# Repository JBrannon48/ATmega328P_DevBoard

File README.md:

# ATmega328P_DevBoard
Created By: Jack Brannon
Made this in a day for Purdue SoCET: Intro I.

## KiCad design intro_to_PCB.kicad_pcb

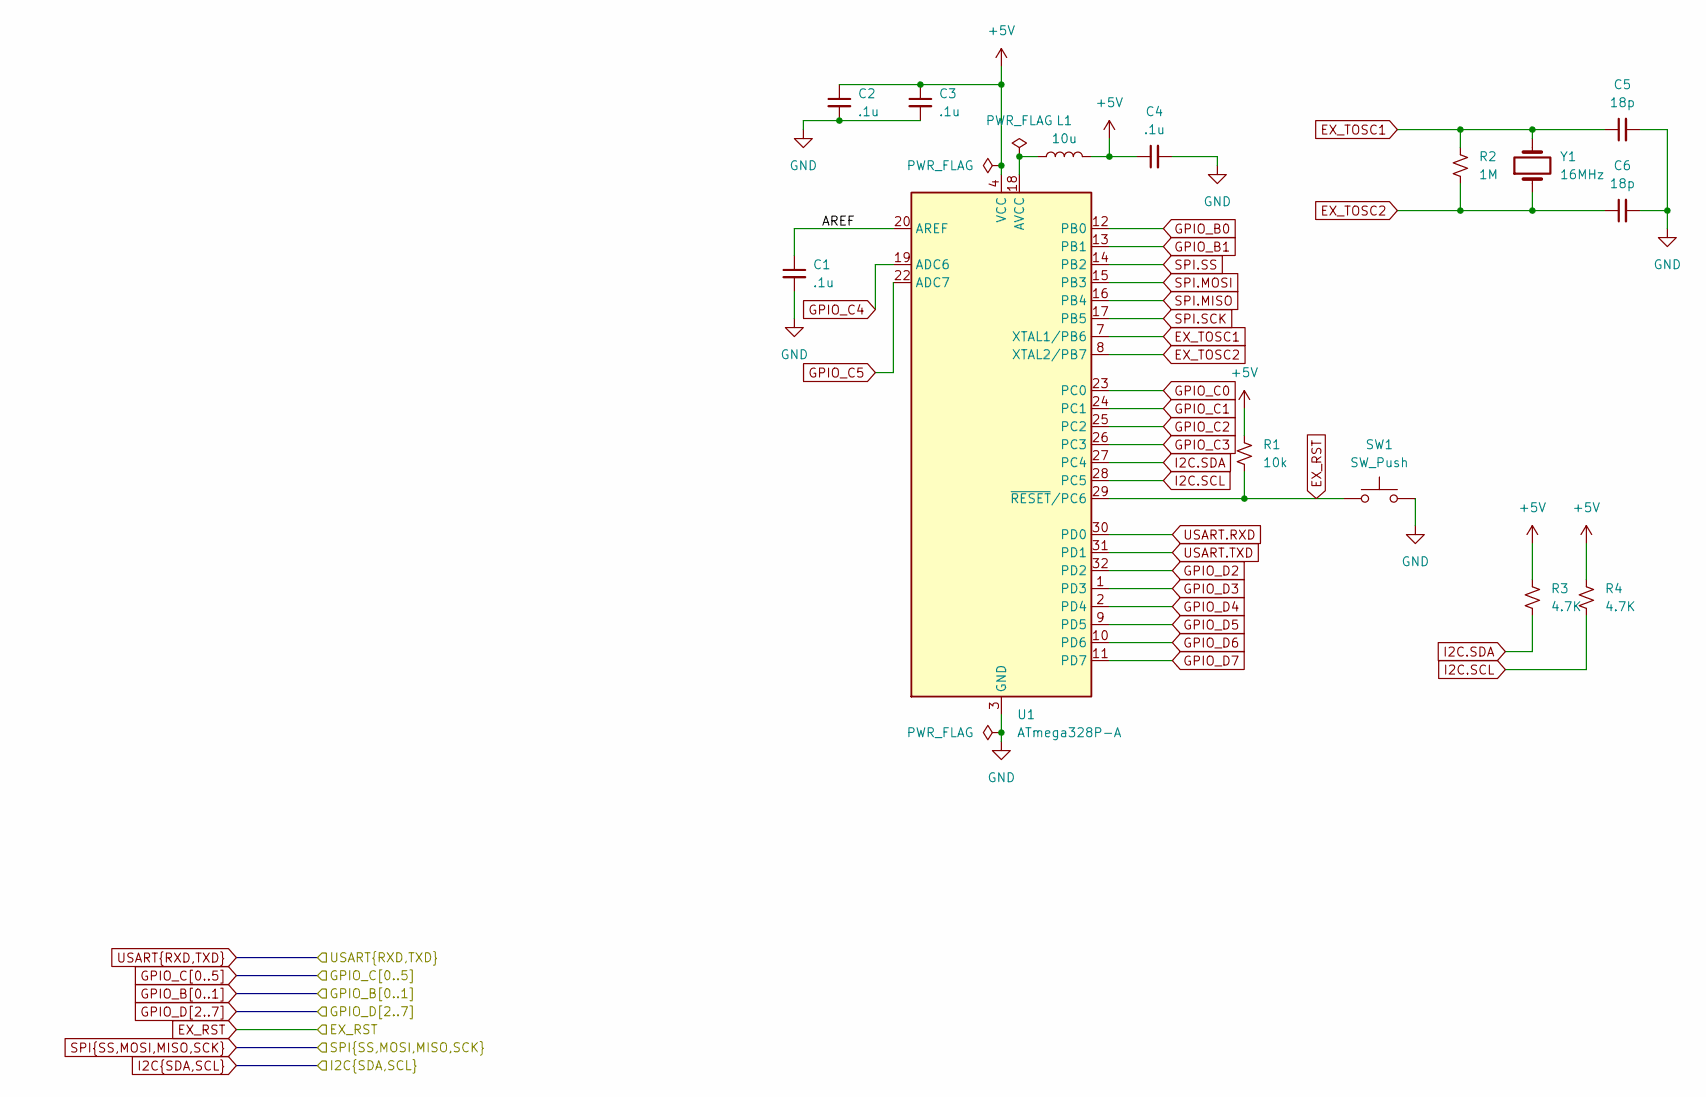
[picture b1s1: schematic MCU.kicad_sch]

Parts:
C1, C2, C3, C4: .1u; C_0402_1005Metric
C5, C6: 18p; C_0402_1005Metric
L1: 10u; L_0603_1608Metric
R1: 10k; R_0402_1005Metric
R2: 1M; R_0402_1005Metric
R3, R4: 4.7K; R_0402_1005Metric
SW1: SW_Push; SW_Push_SPST_NO_Alps_SKRK
U1: ATmega328P-A; TQFP-32_7x7mm_P0.8mm
Y1: 16MHz; Crystal_SMD_2012-2Pin_2.0x1.2mm

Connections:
+5V: C2.1, C3.1, C4.1, L1.2, R1.1, R3.1, R4.1, U1.4 (VCC), U1.6 (VCC); also elsewhere on the board
/MCU/AREF: C1.1, U1.20 (AREF)
EX_RST: R1.2, SW1.1, U1.29 (~RESET/PC6); also elsewhere on the board
EX_TOSC1: C5.1, R2.1, U1.7 (XTAL1/PB6), Y1.2
EX_TOSC2: C6.1, R2.2, U1.8 (XTAL2/PB7), Y1.1
GND: C1.2, C2.2, C3.2, C4.2, C5.2, C6.2, SW1.2, U1.3 (GND), U1.5 (GND), U1.21 (GND); also elsewhere on the board
GPIO_B0: U1.12 (PB0); also elsewhere on the board
GPIO_B1: U1.13 (PB1); also elsewhere on the board
GPIO_C0: U1.23 (PC0); also elsewhere on the board
GPIO_C1: U1.24 (PC1); also elsewhere on the board
GPIO_C2: U1.25 (PC2); also elsewhere on the board
GPIO_C3: U1.26 (PC3); also elsewhere on the board
GPIO_C4: U1.19 (ADC6); also elsewhere on the board
GPIO_C5: U1.22 (ADC7); also elsewhere on the board
GPIO_D2: U1.32 (PD2); also elsewhere on the board
GPIO_D3: U1.1 (PD3); also elsewhere on the board
GPIO_D4: U1.2 (PD4); also elsewhere on the board
GPIO_D5: U1.9 (PD5); also elsewhere on the board
GPIO_D6: U1.10 (PD6); also elsewhere on the board
GPIO_D7: U1.11 (PD7); also elsewhere on the board
I2C.SCL: R4.2, U1.28 (PC5); also elsewhere on the board
I2C.SDA: R3.2, U1.27 (PC4); also elsewhere on the board
unnamed: L1.1, U1.18 (AVCC)
SPI.MISO: U1.16 (PB4); also elsewhere on the board
SPI.MOSI: U1.15 (PB3); also elsewhere on the board
SPI.SCK: U1.17 (PB5); also elsewhere on the board
SPI.SS: U1.14 (PB2); also elsewhere on the board
USART.RXD: U1.30 (PD0); also elsewhere on the board
USART.TXD: U1.31 (PD1); also elsewhere on the board

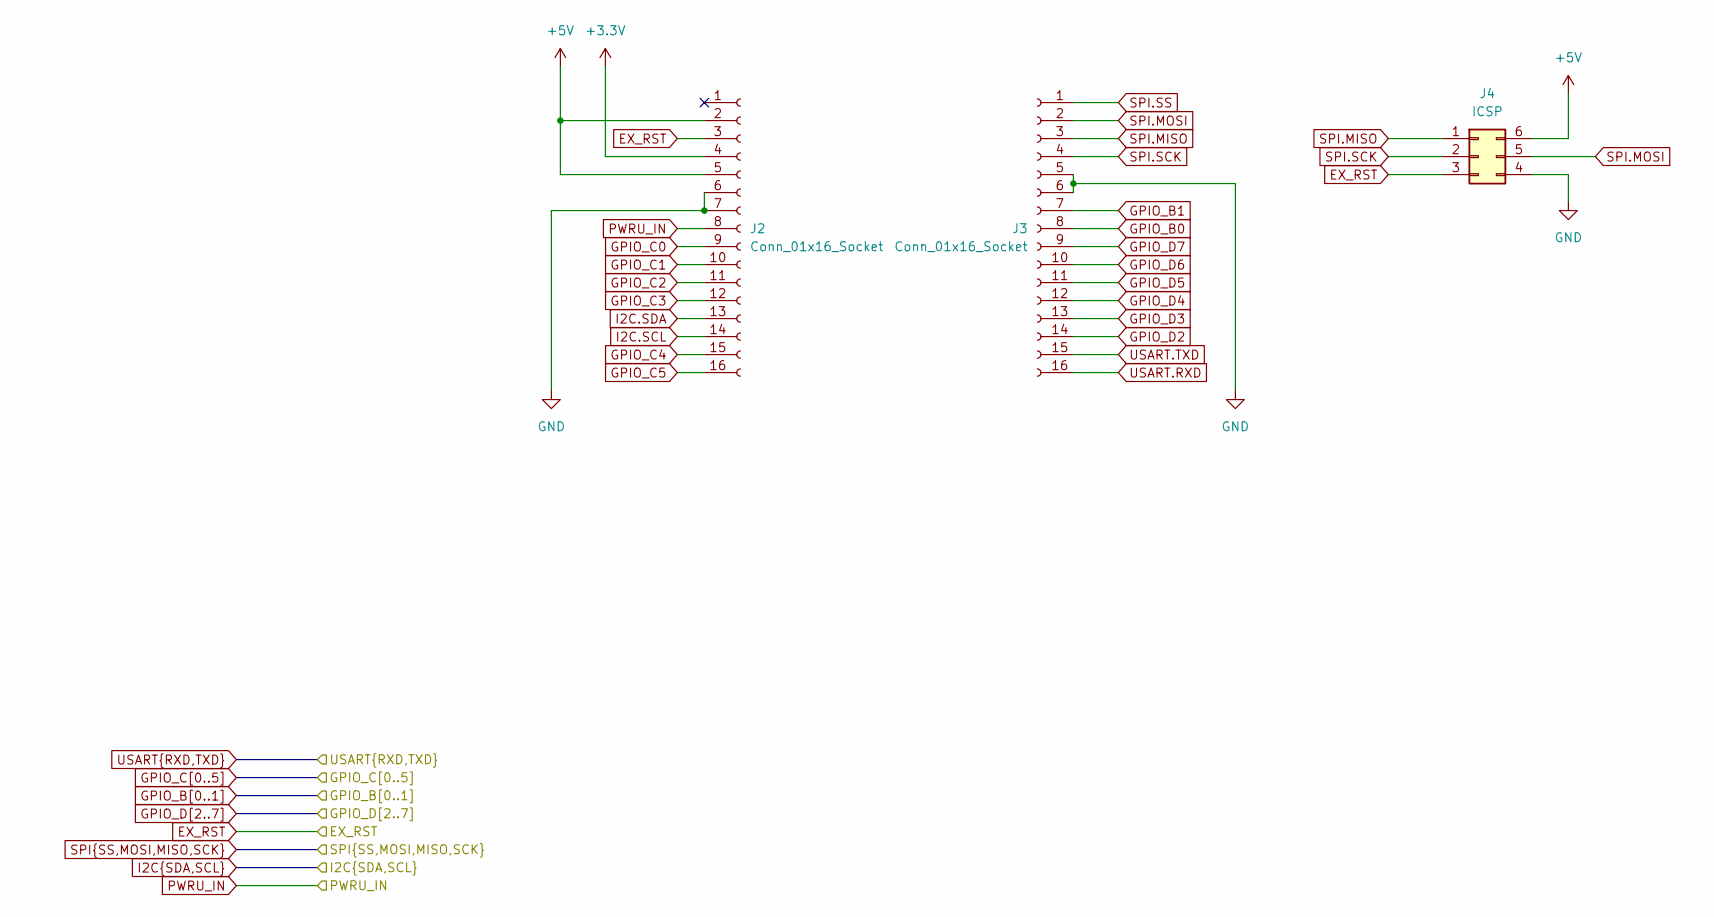
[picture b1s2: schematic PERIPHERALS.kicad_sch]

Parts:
J2, J3: Conn_01x16_Socket; PinHeader_1x16_P2.54mm_Vertical
J4: ICSP; PinHeader_2x03_P2.54mm_Vertical

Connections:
+3.3V: J2.4; also elsewhere on the board
+5V: J2.2, J2.5, J4.6; also elsewhere on the board
EX_RST: J2.3, J4.3; also elsewhere on the board
GND: J2.6, J2.7, J3.5, J3.6, J4.4; also elsewhere on the board
GPIO_B0: J3.8; also elsewhere on the board
GPIO_B1: J3.7; also elsewhere on the board
GPIO_C0: J2.9; also elsewhere on the board
GPIO_C1: J2.10; also elsewhere on the board
GPIO_C2: J2.11; also elsewhere on the board
GPIO_C3: J2.12; also elsewhere on the board
GPIO_C4: J2.15; also elsewhere on the board
GPIO_C5: J2.16; also elsewhere on the board
GPIO_D2: J3.14; also elsewhere on the board
GPIO_D3: J3.13; also elsewhere on the board
GPIO_D4: J3.12; also elsewhere on the board
GPIO_D5: J3.11; also elsewhere on the board
GPIO_D6: J3.10; also elsewhere on the board
GPIO_D7: J3.9; also elsewhere on the board
I2C.SCL: J2.14; also elsewhere on the board
I2C.SDA: J2.13; also elsewhere on the board
PWRU_IN: J2.8; also elsewhere on the board
SPI.MISO: J3.3, J4.1; also elsewhere on the board
SPI.MOSI: J3.2, J4.5; also elsewhere on the board
SPI.SCK: J3.4, J4.2; also elsewhere on the board
SPI.SS: J3.1; also elsewhere on the board
USART.RXD: J3.16; also elsewhere on the board
USART.TXD: J3.15; also elsewhere on the board

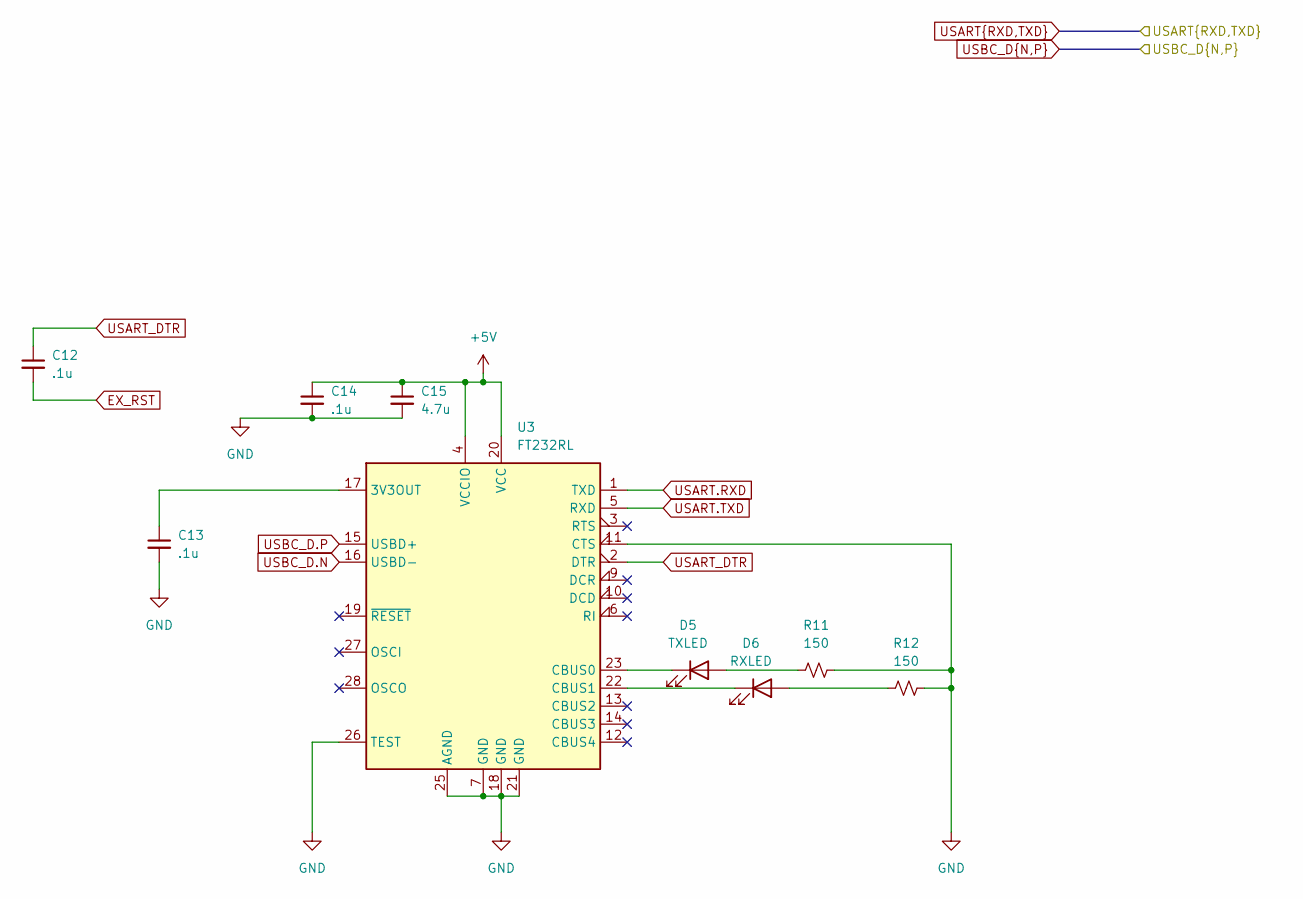
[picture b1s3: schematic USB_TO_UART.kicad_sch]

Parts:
C12, C13: .1u; C_0402_1005Metric_Pad0.74x0.62mm_HandSolder
C14: .1u; C_Elec_6.3x7.7
C15: 4.7u; C_Elec_6.3x7.7
D5: TXLED; LED_0402_1005Metric
D6: RXLED; LED_0402_1005Metric
R11, R12: 150; R_0402_1005Metric
U3: FT232RL; SSOP-28_5.3x10.2mm_P0.65mm

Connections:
+5V: C14.1, C15.1, U3.4 (VCCIO), U3.20 (VCC); also elsewhere on the board
EX_RST: C12.2; also elsewhere on the board
GND: C13.2, C14.2, C15.2, R11.2, R12.2, U3.7 (GND), U3.11 (CTS), U3.18 (GND), U3.21 (GND), U3.25 (AGND), U3.26 (TEST); also elsewhere on the board
unnamed: D5.2 (A), R11.1
unnamed: D5.1 (K), U3.23 (CBUS0)
unnamed: D6.2 (A), R12.1
unnamed: D6.1 (K), U3.22 (CBUS1)
unnamed: C13.1, U3.17 (3V3OUT)
USART.RXD: U3.1 (TXD); also elsewhere on the board
USART.TXD: U3.5 (RXD); also elsewhere on the board
USART_DTR: C12.1, U3.2 (DTR)
USBC_D.N: U3.16 (USBD-); also elsewhere on the board
USBC_D.P: U3.15 (USBD+); also elsewhere on the board

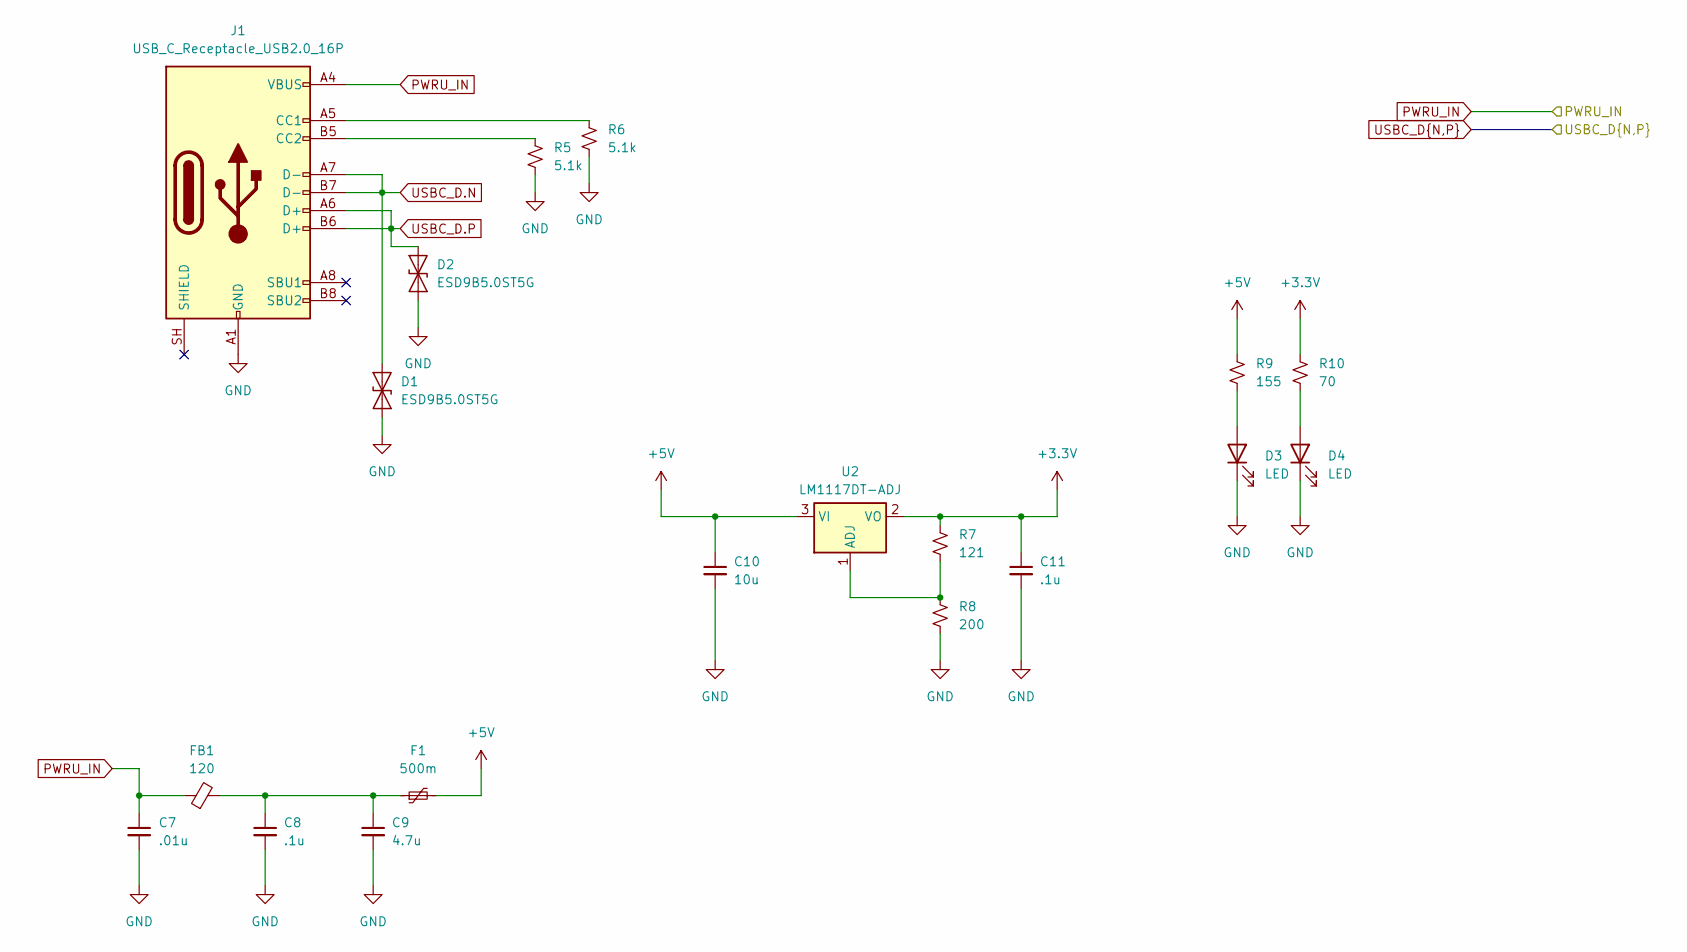
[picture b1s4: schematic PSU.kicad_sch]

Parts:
C7: .01u; C_0603_1608Metric
C8: .1u; C_0402_1005Metric
C9: 4.7u; C_Elec_6.3x7.7
C10: 10u; C_Elec_6.3x7.7
C11: .1u; C_Elec_6.3x7.7
D1, D2: ESD9B5.0ST5G; D_SOD-923
D3, D4: LED; LED_0402_1005Metric
F1: 500m; Fuse_1812_4532Metric
FB1: 120; L_0603_1608Metric
J1: USB_C_Receptacle_USB2.0_16P; USB_C_Receptacle_Palconn_UTC16-G
R5, R6: 5.1k; R_0402_1005Metric
R7: 121; R_0402_1005Metric
R8: 200; R_0402_1005Metric
R9: 155; R_0402_1005Metric
R10: 70; R_0402_1005Metric
U2: LM1117DT-ADJ; TO-252-3_TabPin2

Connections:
+3.3V: C11.1, R7.1, R10.1, U2.2 (VO); also elsewhere on the board
+5V: C10.1, F1.2, R9.1, U2.3 (VI); also elsewhere on the board
GND: C7.2, C8.2, C9.2, C10.2, C11.2, D1.1 (A1), D2.1 (A1), D3.1 (K), D4.1 (K), J1.A1 (GND), J1.A12 (GND), J1.B1 (GND), J1.B12 (GND), R5.2, R6.2, R8.2; also elsewhere on the board
unnamed: C8.1, C9.1, F1.1, FB1.2
unnamed: D3.2 (A), R9.2
unnamed: D4.2 (A), R10.2
unnamed: J1.A5 (CC1), R6.1
unnamed: J1.B5 (CC2), R5.1
unnamed: R7.2, R8.1, U2.1 (ADJ)
PWRU_IN: C7.1, FB1.1, J1.A4 (VBUS), J1.A9 (VBUS), J1.B4 (VBUS), J1.B9 (VBUS); also elsewhere on the board
USBC_D.N: D1.2 (A2), J1.A7 (D-), J1.B7 (D-); also elsewhere on the board
USBC_D.P: D2.2 (A2), J1.A6 (D+), J1.B6 (D+); also elsewhere on the board

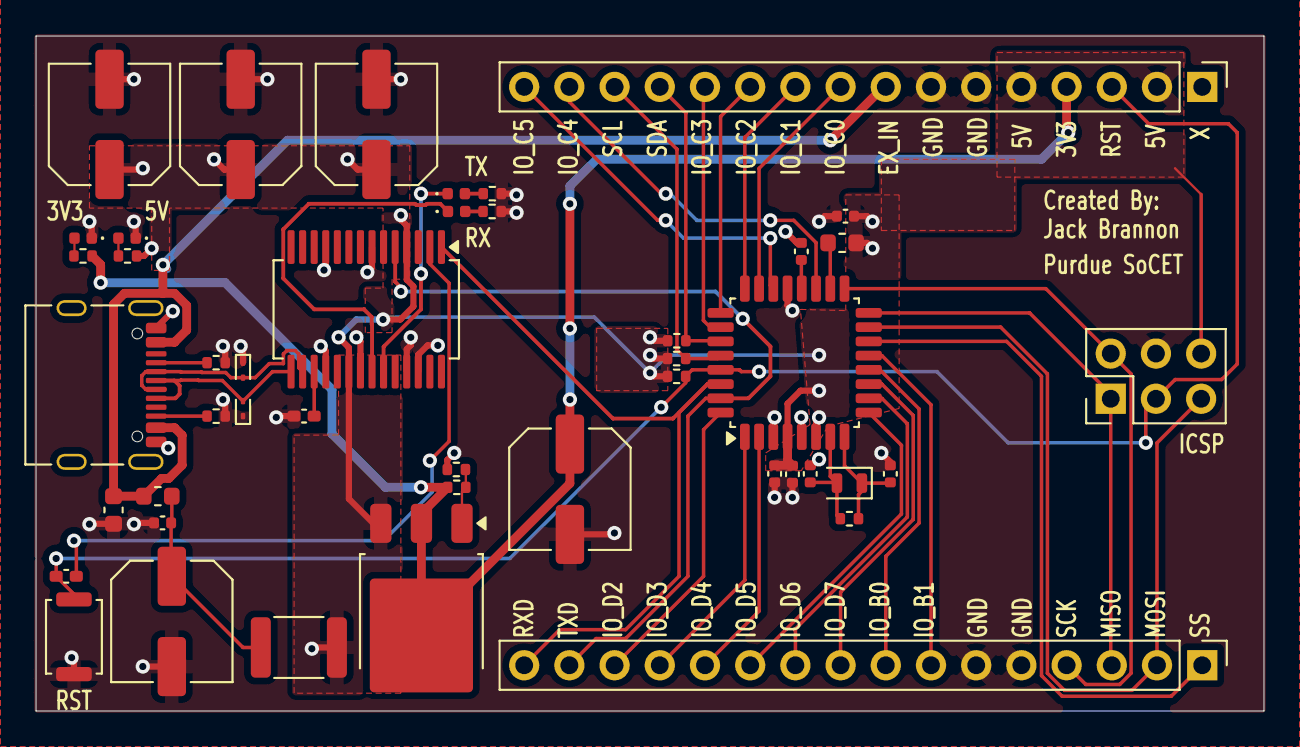
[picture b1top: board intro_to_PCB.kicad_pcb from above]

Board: 2 copper layers, 69.0 x 37.9 mm, 45 parts (0 on the bottom side), 45 nets.

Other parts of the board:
ICSP: ICSP; PinHeader_2x03_P2.54mm_Vertical

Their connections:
+5V: ICSP.6; also elsewhere on the board
EX_RST: ICSP.3; also elsewhere on the board
GND: ICSP.4; also elsewhere on the board
SPI.MISO: ICSP.1; also elsewhere on the board
SPI.MOSI: ICSP.5; also elsewhere on the board
SPI.SCK: ICSP.2; also elsewhere on the board

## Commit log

2026-04-20 Initial Commit
    I did the project without version control lol
2026-04-20 PCB preview on KiCanvas wasnt working
2026-04-20 Add creator and project description to README
